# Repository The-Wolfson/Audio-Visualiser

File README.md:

# Audio Visualiser
A desktop device to control Spotify, with some bonus nifty visuals. Built for [hackclub's grounded YSWS](grounded.hackclub.com).

## Operation
The device features 4 input methods; a rotary encoder for volume, and back/pause/skip buttons to control audio playback.

The screen displays the current playing song, as well as other relevant information.

The LED matrix shows a realtime representation of the audio spectrum.

## Future Features
- [ ] Speaker
- [ ] Microphone
- [ ] Audio Jack

## BOM
| Part | Model | ID | Quantity | Price (USD)|
|-|-|-|-|-|
| PCB | - | - |1| 4 |
| Case | - | - |1| 8 |
| Screws | M6x20 | - | 4 |5 |
Screen | GME12864-11, SSD1306 | large-screen |2|-
Button | Kailh Box White Pro | switches | 2
LED Matrix | MAX7219 8x8 LED Dot Matrix Display Module | led-matrix | 3
Microcontroller | Seeed Studio XIAO ESP32C3 | Xiao-esp32 | 1
Rotary Encoder | EC11 Rotary Encoder with Switch | encoder | 1
Diode | 1N4148 | diodes | 4

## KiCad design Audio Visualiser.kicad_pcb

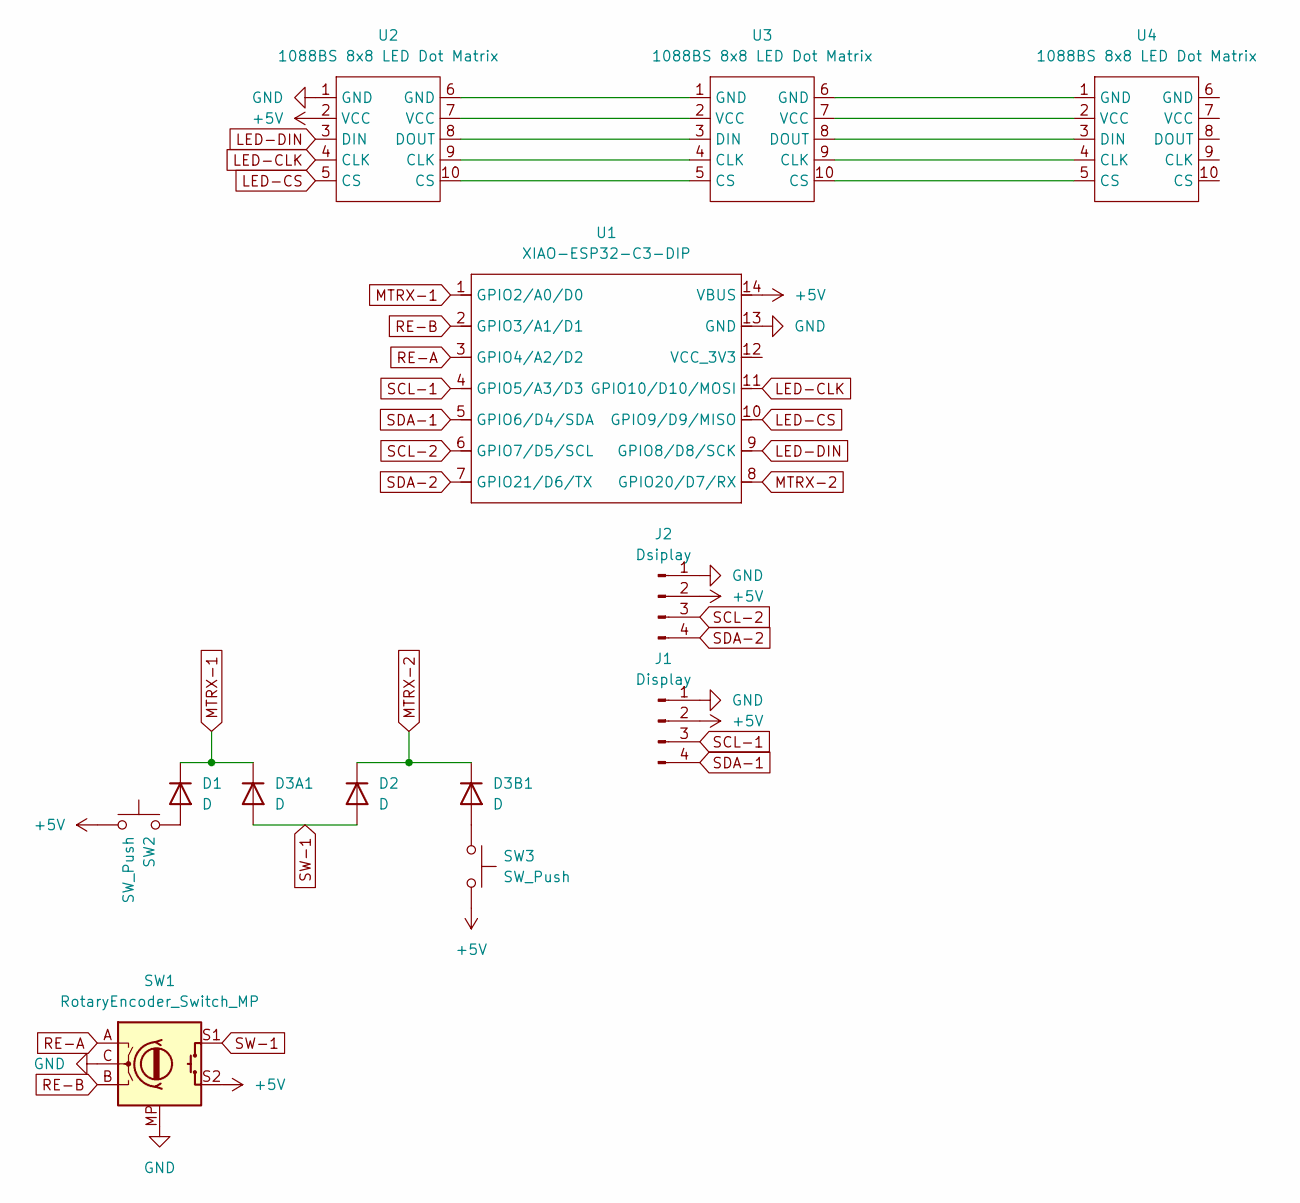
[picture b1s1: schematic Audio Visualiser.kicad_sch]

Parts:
D1, D2, D3A1, D3B1: D; D_DO-35_SOD27_P7.62mm_Horizontal
J1: Display; OLED_SSD1306_I2C_0.96
J2: Dsiplay; OLED_SSD1306_I2C_0.96
SW1: RotaryEncoder_Switch_MP; RotaryEncoder_Alps_EC11E-Switch_Vertical_H20mm
SW2, SW3: SW_Push; SW_Cherry_MX_PCB
U1: XIAO-ESP32-C3-DIP; XIAO-ESP32C3-DIP
U2, U3, U4: 1088BS 8x8 LED Dot Matrix; 8x8 LED Dot Matrix Display Module

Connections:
+5V: J1.2, J2.2, SW1.S2, SW2.1, SW3.2, U1.14 (VBUS), U2.2 (VCC)
GND: J1.1, J2.1, SW1.C, SW1.MP, U1.13 (GND), U2.1 (GND)
LED-CLK: U1.11 (GPIO10/D10/MOSI), U2.4 (CLK)
LED-CS: U1.10 (GPIO9/D9/MISO), U2.5 (CS)
LED-DIN: U1.9 (GPIO8/D8/SCK), U2.3 (DIN)
MTRX-1: D1.1 (K), D3A1.1 (K), U1.1 (GPIO2/A0/D0)
MTRX-2: D2.1 (K), D3B1.1 (K), U1.8 (GPIO20/D7/RX)
unnamed: D1.2 (A), SW2.2
unnamed: D3B1.2 (A), SW3.1
unnamed: U2.9 (CLK), U3.4 (CLK)
unnamed: U2.10 (CS), U3.5 (CS)
unnamed: U2.8 (DOUT), U3.3 (DIN)
unnamed: U2.6 (GND), U3.1 (GND)
unnamed: U2.7 (VCC), U3.2 (VCC)
unnamed: U3.9 (CLK), U4.4 (CLK)
unnamed: U3.10 (CS), U4.5 (CS)
unnamed: U3.8 (DOUT), U4.3 (DIN)
unnamed: U3.6 (GND), U4.1 (GND)
unnamed: U3.7 (VCC), U4.2 (VCC)
RE-A: SW1.A, U1.3 (GPIO4/A2/D2)
RE-B: SW1.B, U1.2 (GPIO3/A1/D1)
SCL-1: J1.3, U1.4 (GPIO5/A3/D3)
SCL-2: J2.3, U1.6 (GPIO7/D5/SCL)
SDA-1: J1.4, U1.5 (GPIO6/D4/SDA)
SDA-2: J2.4, U1.7 (GPIO21/D6/TX)
SW-1: D2.2 (A), D3A1.2 (A), SW1.S1

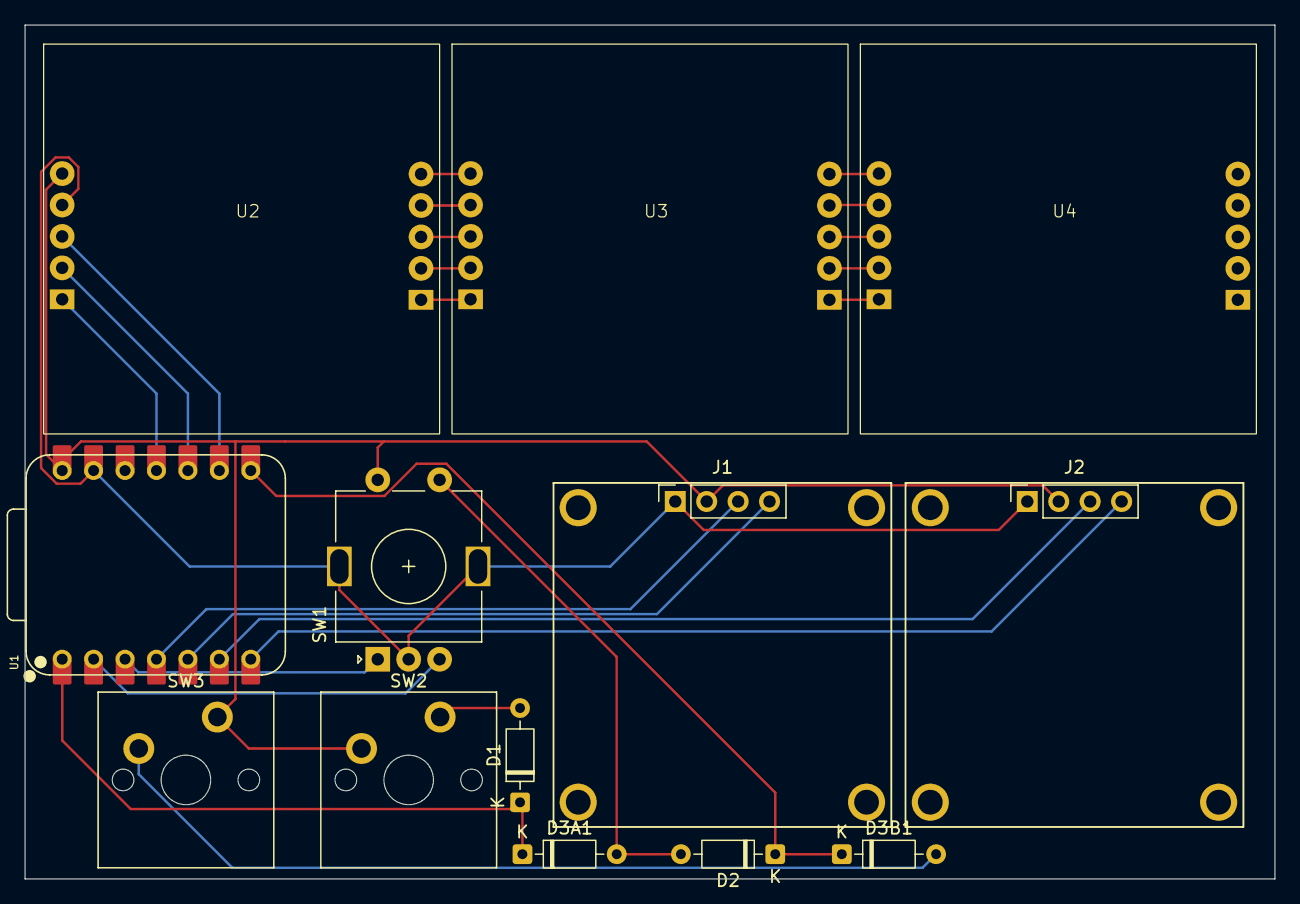
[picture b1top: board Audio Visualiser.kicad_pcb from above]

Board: 2 copper layers, 101.0 x 69.0 mm, 13 parts (0 on the bottom side), 26 nets.

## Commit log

2025-08-19 added Journal and README
2025-08-20 rearranged the schematic
